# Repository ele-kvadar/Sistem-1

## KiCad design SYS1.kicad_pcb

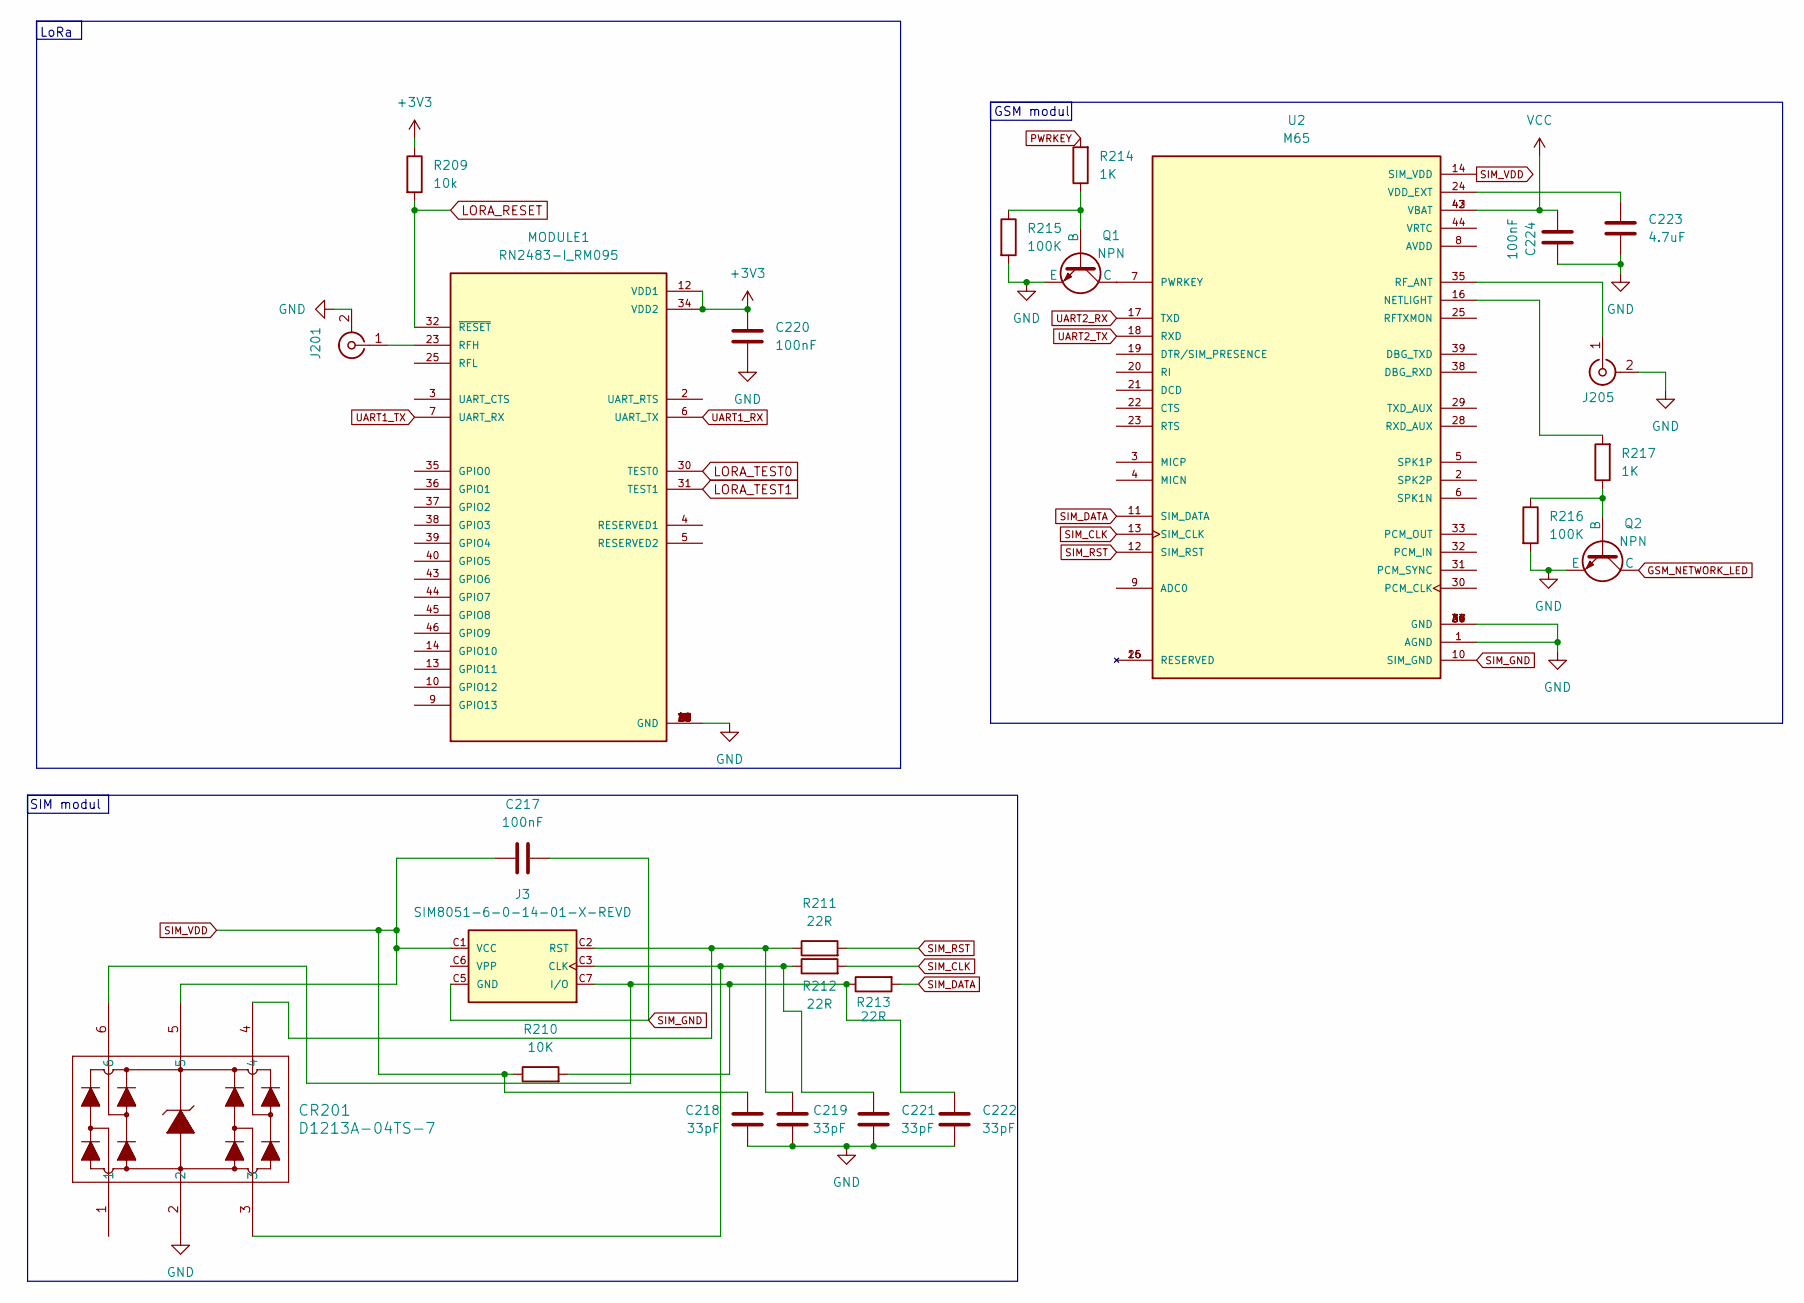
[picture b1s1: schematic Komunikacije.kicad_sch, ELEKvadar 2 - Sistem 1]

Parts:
C217, C220, C224: 100nF; C_1206_3216Metric_Pad1.33x1.80mm_HandSolder
C218, C219, C221, C222: 33pF; C_1206_3216Metric_Pad1.33x1.80mm_HandSolder
C223: 4.7uF; C_1206_3216Metric_Pad1.33x1.80mm_HandSolder
CR201: D1213A-04TS-7; TSOT26_DIO
J3: SIM8051-6-0-14-01-X-REVD; GCT_SIM8051-6-0-14-01-X-REVD
J201, J205: SMA_Amphenol_132134-16_Vertical
MODULE1: RN2483-I_RM095; MICROCHIP_RN2483-I_RM095
Q1, Q2: NPN; TSOT-23_HandSoldering
R209: 10k; R_1206_3216Metric_Pad1.30x1.75mm_HandSolder
R210: 10K; R_1206_3216Metric_Pad1.30x1.75mm_HandSolder
R211, R212, R213: 22R; R_1206_3216Metric_Pad1.30x1.75mm_HandSolder
R214, R217: 1K; R_1206_3216Metric_Pad1.30x1.75mm_HandSolder
R215, R216: 100K; R_1206_3216Metric_Pad1.30x1.75mm_HandSolder
U2: M65; XCVR_M65; PARTREV 1.0

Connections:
GND: C218.2, C219.2, C220.2, C221.2, C222.2, C223.1, C224.1, CR201.2, J201.2 (Ext), J205.2 (Ext), MODULE1.1 (GND), MODULE1.8 (GND), MODULE1.11 (GND), MODULE1.20 (GND), MODULE1.21 (GND), MODULE1.22 (GND), MODULE1.24 (GND), MODULE1.26 (GND), MODULE1.27 (GND), MODULE1.28 (GND), MODULE1.33 (GND), MODULE1.41 (GND), MODULE1.47 (GND), Q1.3 (E), Q2.3 (E), R215.2, R216.2, U2.1 (AGND), U2.27 (GND), U2.34 (GND), U2.36 (GND), U2.37 (GND), U2.40 (GND), U2.41 (GND); also elsewhere on the board
GSM_NETWORK_LED: Q2.1 (C); also elsewhere on the board
LORA_RESET: MODULE1.32 (~RESET), R209.2; also elsewhere on the board
LORA_TEST0: MODULE1.30 (TEST0); also elsewhere on the board
LORA_TEST1: MODULE1.31 (TEST1); also elsewhere on the board
unnamed: C221.1, CR201.3, J3.C3 (CLK), R212.1
unnamed: C222.1, CR201.6, J3.C7 (I/O), R210.2, R213.1
unnamed: C219.1, CR201.4, J3.C2 (RST), R211.1
unnamed: J201.1 (In), MODULE1.23 (RFH)
unnamed: J205.1 (In), U2.35 (RF_ANT)
unnamed: Q1.2 (B), R214.1, R215.1
unnamed: Q1.1 (C), U2.7 (PWRKEY)
unnamed: Q2.2 (B), R216.1, R217.1
unnamed: R217.2, U2.16 (NETLIGHT)
unnamed: C223.2, U2.24 (VDD_EXT)
PWRKEY: R214.2; also elsewhere on the board
SIM_CLK: R212.2, U2.13 (SIM_CLK)
SIM_DATA: R213.2, U2.11 (SIM_DATA)
SIM_GND: C217.2, J3.C5 (GND), U2.10 (SIM_GND)
SIM_RST: R211.2, U2.12 (SIM_RST)
SIM_VDD: C217.1, C218.1, CR201.5, J3.C1 (VCC), R210.1, U2.14 (SIM_VDD)
UART1_RX: MODULE1.6 (UART_TX); also elsewhere on the board
UART1_TX: MODULE1.7 (UART_RX); also elsewhere on the board
UART2_RX: U2.17 (TXD); also elsewhere on the board
UART2_TX: U2.18 (RXD); also elsewhere on the board
VCC: C224.2, U2.42 (VBAT), U2.43 (VBAT); also elsewhere on the board
VDDA: C220.1, MODULE1.12 (VDD1), MODULE1.34 (VDD2), R209.1; also elsewhere on the board

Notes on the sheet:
SIM modul
GSM modul
LoRa

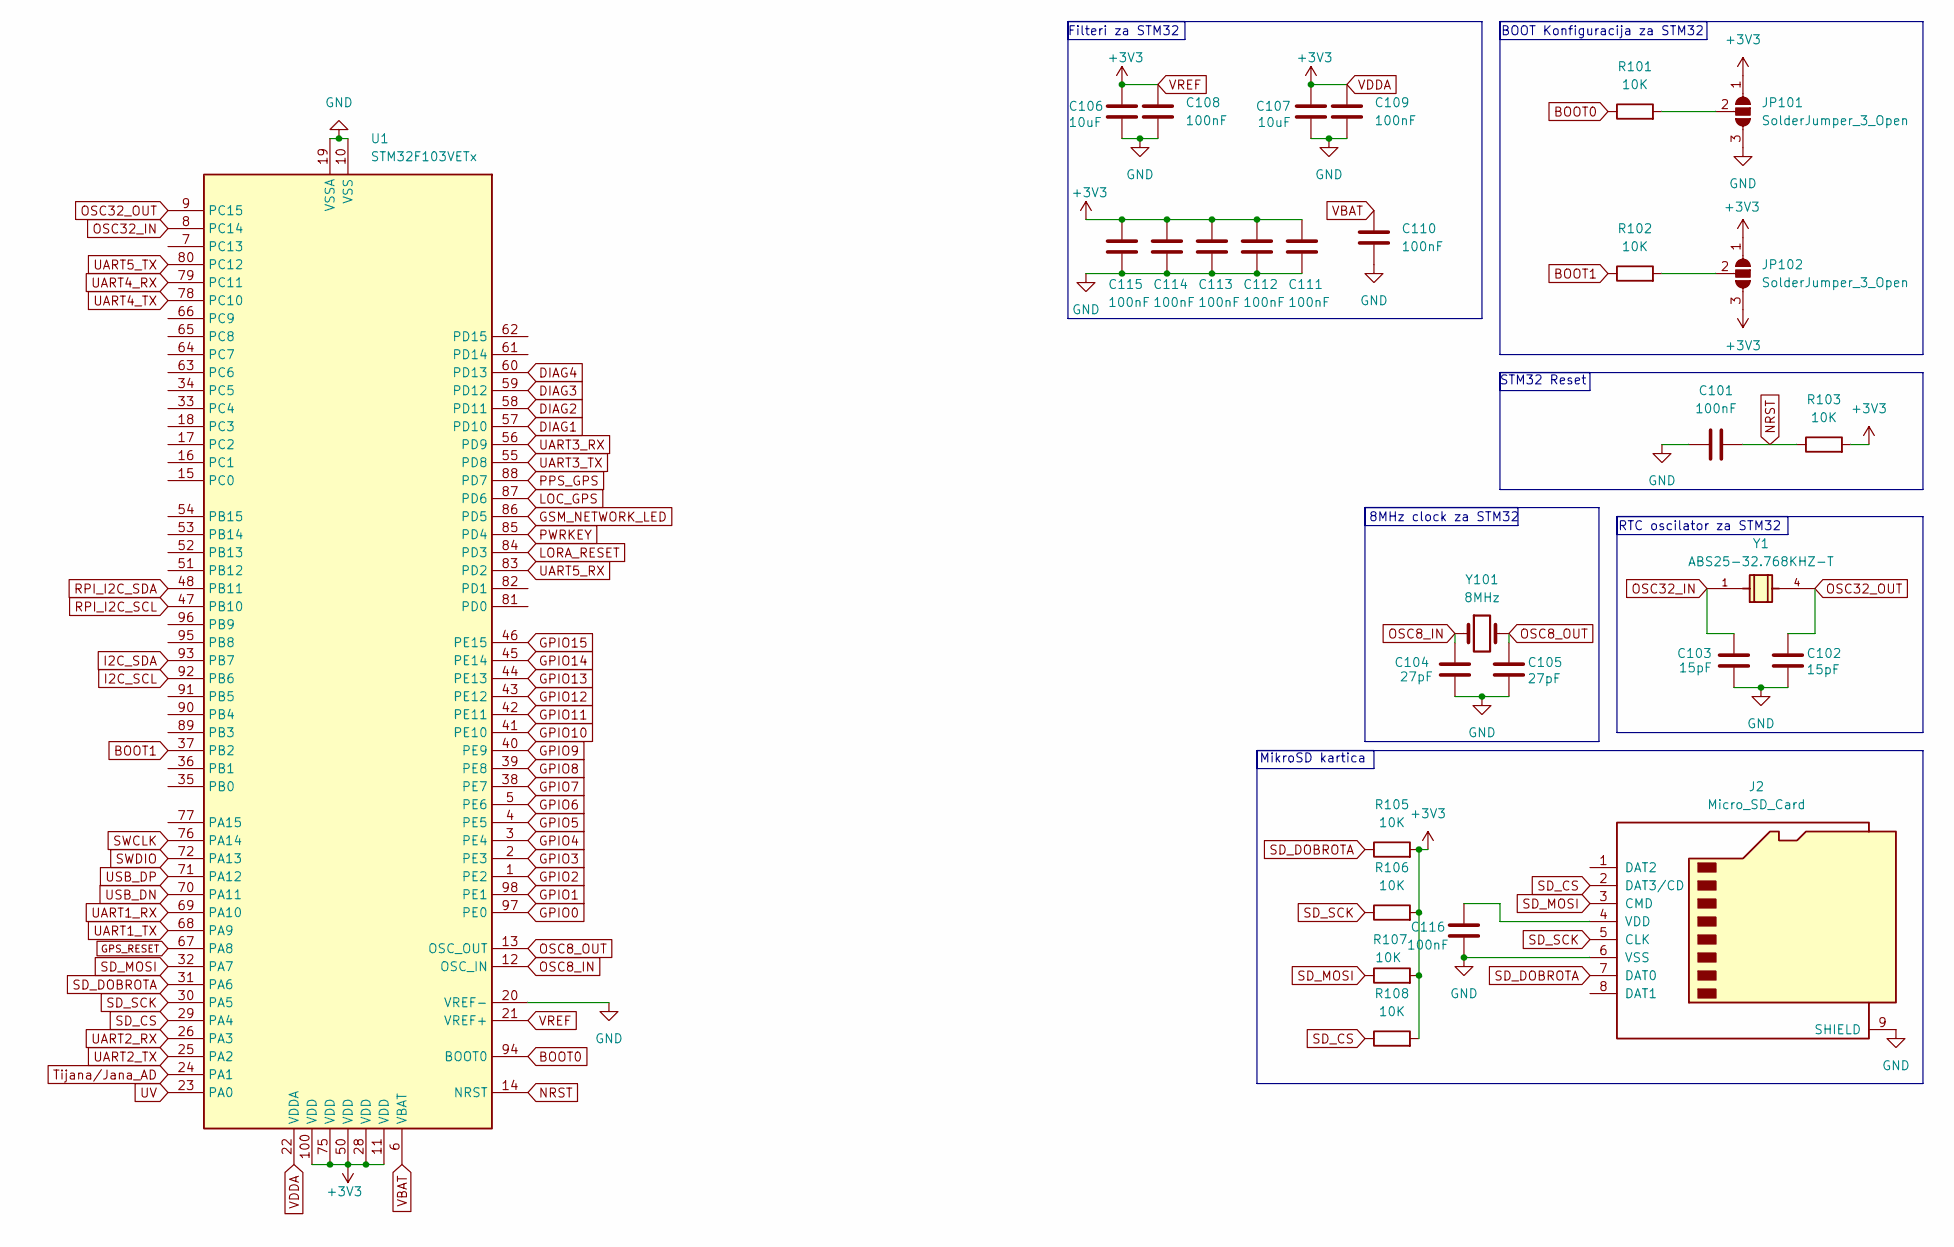
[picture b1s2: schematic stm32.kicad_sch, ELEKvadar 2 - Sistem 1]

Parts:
C101, C108, C109, C110, C111, C112, C113, C114, C115, C116: 100nF; C_1206_3216Metric_Pad1.33x1.80mm_HandSolder
C102, C103: 15pF; C_1206_3216Metric_Pad1.33x1.80mm_HandSolder
C104, C105: 27pF; C_1206_3216Metric_Pad1.33x1.80mm_HandSolder
C106, C107: 10uF; C_1206_3216Metric_Pad1.33x1.80mm_HandSolder
J2: Micro_SD_Card; microSD_HC_Molex_47219-2001
JP101, JP102: SolderJumper_3_Open; SolderJumper-3_P1.3mm_Open_RoundedPad1.0x1.5mm
R101, R102, R103, R105, R106, R107, R108: 10K; R_1206_3216Metric_Pad1.30x1.75mm_HandSolder
U1: STM32F103VETx; LQFP-100_14x14mm_P0.5mm
Y1: ABS25-32.768KHZ-T; Crystal_SMD_Abracon_ABS25-4Pin_8.0x3.8mm; PARTREV 12.01.15
Y101: 8MHz; Crystal_SMD_HC49-SD

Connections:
BOOT0: R101.1, U1.94 (BOOT0)
BOOT1: R102.1, U1.37 (PB2)
DIAG1: U1.57 (PD10); also elsewhere on the board
DIAG2: U1.58 (PD11); also elsewhere on the board
DIAG3: U1.59 (PD12); also elsewhere on the board
DIAG4: U1.60 (PD13); also elsewhere on the board
GND: C101.1, C102.2, C103.2, C104.2, C105.2, C106.2, C107.2, C108.1, C109.1, C110.1, C111.1, C112.1, C113.1, C114.1, C115.1, C116.1, J2.6 (VSS), J2.9 (SHIELD), JP101.3 (B), U1.10 (VSS), U1.19 (VSSA), U1.20 (VREF-), U1.27 (VSS), U1.49 (VSS), U1.74 (VSS), U1.99 (VSS); also elsewhere on the board
GPIO0: U1.97 (PE0); also elsewhere on the board
GPIO1: U1.98 (PE1); also elsewhere on the board
GPIO2: U1.1 (PE2); also elsewhere on the board
GPIO3: U1.2 (PE3); also elsewhere on the board
GPIO4: U1.3 (PE4); also elsewhere on the board
GPIO5: U1.4 (PE5); also elsewhere on the board
GPIO6: U1.5 (PE6); also elsewhere on the board
GPIO7: U1.38 (PE7); also elsewhere on the board
GPIO8: U1.39 (PE8); also elsewhere on the board
GPIO9: U1.40 (PE9); also elsewhere on the board
GPIO10: U1.41 (PE10); also elsewhere on the board
GPIO11: U1.42 (PE11); also elsewhere on the board
GPIO12: U1.43 (PE12); also elsewhere on the board
GPIO13: U1.44 (PE13); also elsewhere on the board
GPIO14: U1.45 (PE14); also elsewhere on the board
GPIO15: U1.46 (PE15); also elsewhere on the board
GPS_RESET: U1.67 (PA8); also elsewhere on the board
GSM_NETWORK_LED: U1.86 (PD5); also elsewhere on the board
I2C_SCL: U1.92 (PB6); also elsewhere on the board
I2C_SDA: U1.93 (PB7); also elsewhere on the board
LOC_GPS: U1.87 (PD6); also elsewhere on the board
LORA_RESET: U1.84 (PD3); also elsewhere on the board
NRST: C101.2, R103.1, U1.14 (NRST); also elsewhere on the board
unnamed: C116.2, J2.4 (VDD)
unnamed: JP101.2 (C), R101.2
unnamed: JP102.2 (C), R102.2
OSC8_IN: C104.1, U1.12 (OSC_IN), Y101.1
OSC8_OUT: C105.1, U1.13 (OSC_OUT), Y101.2
OSC32_IN: C103.1, U1.8 (PC14), Y1.1
OSC32_OUT: C102.1, U1.9 (PC15), Y1.4
PPS_GPS: U1.88 (PD7); also elsewhere on the board
PWRKEY: U1.85 (PD4); also elsewhere on the board
RPI_I2C_SCL: U1.47 (PB10); also elsewhere on the board
RPI_I2C_SDA: U1.48 (PB11); also elsewhere on the board
SD_CS: J2.2 (DAT3/CD), R108.1, U1.29 (PA4); also elsewhere on the board
SD_DOBROTA: J2.7 (DAT0), R105.1, U1.31 (PA6); also elsewhere on the board
SD_MOSI: J2.3 (CMD), R107.1, U1.32 (PA7); also elsewhere on the board
SD_SCK: J2.5 (CLK), R106.1, U1.30 (PA5); also elsewhere on the board
SWCLK: U1.76 (PA14); also elsewhere on the board
SWDIO: U1.72 (PA13); also elsewhere on the board
Tijana/Jana_AD: U1.24 (PA1); also elsewhere on the board
UART1_RX: U1.69 (PA10); also elsewhere on the board
UART1_TX: U1.68 (PA9); also elsewhere on the board
UART2_RX: U1.26 (PA3); also elsewhere on the board
UART2_TX: U1.25 (PA2); also elsewhere on the board
UART3_RX: U1.56 (PD9); also elsewhere on the board
UART3_TX: U1.55 (PD8); also elsewhere on the board
UART4_RX: U1.79 (PC11); also elsewhere on the board
UART4_TX: U1.78 (PC10); also elsewhere on the board
UART5_RX: U1.83 (PD2); also elsewhere on the board
UART5_TX: U1.80 (PC12); also elsewhere on the board
USB_DN: U1.70 (PA11); also elsewhere on the board
USB_DP: U1.71 (PA12); also elsewhere on the board
UV: U1.23 (PA0); also elsewhere on the board
VBAT: C110.2, U1.6 (VBAT); also elsewhere on the board
VDDA: C106.1, C107.1, C108.2, C109.2, C111.2, C112.2, C113.2, C114.2, C115.2, JP101.1 (A), JP102.1 (A), JP102.3 (B), R103.2, R105.2, R106.2, R107.2, R108.2, U1.11 (VDD), U1.21 (VREF+), U1.22 (VDDA), U1.28 (VDD), U1.50 (VDD), U1.75 (VDD), U1.100 (VDD); also elsewhere on the board

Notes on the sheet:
STM32 Reset
BOOT Konfiguracija za STM32
8MHz clock za STM32
Filteri za STM32
RTC oscilator za STM32
MikroSD kartica

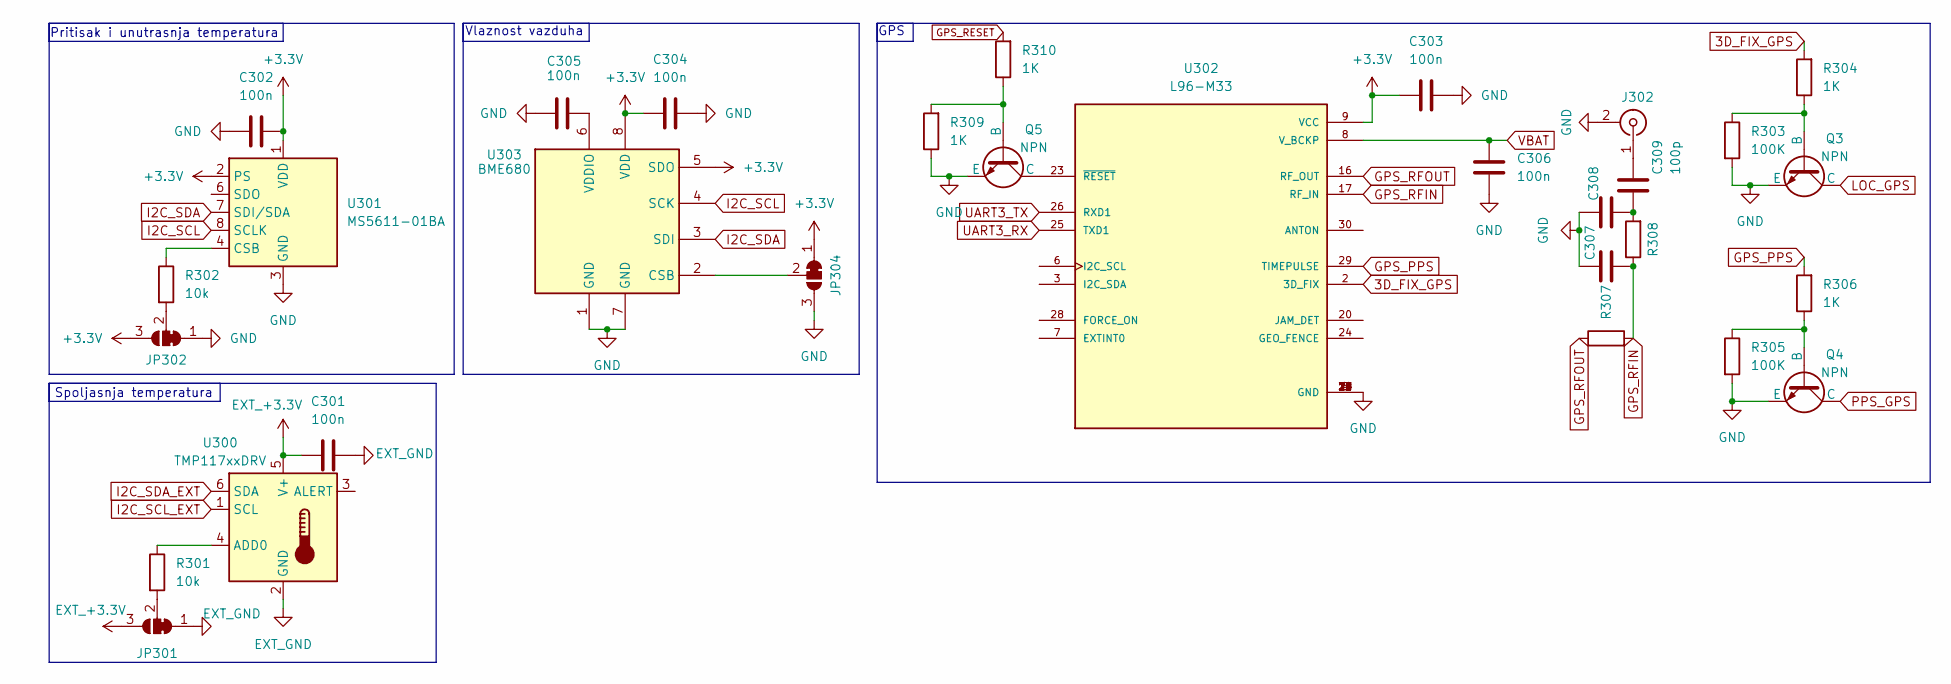
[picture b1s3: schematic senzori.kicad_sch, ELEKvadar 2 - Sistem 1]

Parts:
C301, C302, C303, C304, C305, C306: 100n; C_1206_3216Metric_Pad1.33x1.80mm_HandSolder
C307, C308: 0; C_1206_3216Metric_Pad1.33x1.80mm_HandSolder
C309: 100p; C_1206_3216Metric_Pad1.33x1.80mm_HandSolder
J302: SMA_Amphenol_132134-16_Vertical
JP301, JP302, JP304: SolderJumper_3_Bridged12; SolderJumper-3_P1.3mm_Bridged12_RoundedPad1.0x1.5mm
Q3, Q4, Q5: NPN; TSOT-23_HandSoldering
R301, R302: 10k; R_1206_3216Metric_Pad1.30x1.75mm_HandSolder
R303, R305: 100K; R_1206_3216Metric_Pad1.30x1.75mm_HandSolder
R304, R306, R309, R310: 1K; R_1206_3216Metric_Pad1.30x1.75mm_HandSolder
R307, R308: 0; R_1206_3216Metric_Pad1.30x1.75mm_HandSolder
U300: TMP117xxDRV; WSON-6-1EP_2x2mm_P0.65mm_EP1x1.6mm
U301: MS5611-01BA; LGA-8_3x5mm_P1.25mm
U302: L96-M33; Quectel_L96
U303: BME680; Bosch_LGA-8_3x3mm_P0.8mm_ClockwisePinNumbering

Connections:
3D_FIX_GPS: R304.2, U302.2 (3D_FIX)
+3.3V: C302.2, C303.1, C304.1, JP302.3 (B), JP304.1 (A), U301.1 (VDD), U301.2 (PS), U302.9 (VCC), U303.5 (SDO), U303.8 (VDD); also elsewhere on the board
EXT_+3.3V: C301.1, JP301.3 (B), U300.5 (V+); also elsewhere on the board
EXT_GND: C301.2, JP301.1 (A), U300.2 (GND); also elsewhere on the board
GND: C302.1, C303.2, C304.2, C305.2, C306.2, C307.1, C308.1, J302.2 (Ext), JP302.1 (A), JP304.3 (B), Q3.3 (E), Q4.3 (E), Q5.3 (E), R303.2, R305.2, R309.1, U301.3 (GND), U302.4 (GND), U302.5 (GND), U302.10 (GND), U302.11 (GND), U302.12 (GND), U302.13 (GND), U302.14 (GND), U302.15 (GND), U302.18 (GND), U302.19 (GND), U302.21 (GND), U302.22 (GND), U302.27 (GND), U302.31 (GND), U303.1 (GND), U303.7 (GND); also elsewhere on the board
GPS_PPS: R306.2, U302.29 (TIMEPULSE)
GPS_RESET: R310.2; also elsewhere on the board
GPS_RFIN: C307.2, R307.2, R308.1, U302.17 (RF_IN)
GPS_RFOUT: R307.1, U302.16 (RF_OUT)
I2C_SCL: U301.8 (SCLK), U303.4 (SCK); also elsewhere on the board
I2C_SCL_EXT: U300.1 (SCL); also elsewhere on the board
I2C_SDA: U301.7 (SDI/SDA), U303.3 (SDI); also elsewhere on the board
I2C_SDA_EXT: U300.6 (SDA); also elsewhere on the board
LOC_GPS: Q3.1 (C); also elsewhere on the board
unnamed: C308.2, C309.2, R308.2
unnamed: C309.1, J302.1 (In)
unnamed: JP301.2 (C), R301.2
unnamed: JP302.2 (C), R302.2
unnamed: JP304.2 (C), U303.2 (CSB)
unnamed: Q3.2 (B), R303.1, R304.1
unnamed: Q4.2 (B), R305.1, R306.1
unnamed: Q5.2 (B), R309.2, R310.1
unnamed: Q5.1 (C), U302.23 (~RESET)
unnamed: R302.1, U301.4 (CSB), U301.5 (CSB)
unnamed: R301.1, U300.4 (ADD0)
unnamed: C305.1, U303.6 (VDDIO)
PPS_GPS: Q4.1 (C); also elsewhere on the board
UART3_RX: U302.25 (TXD1); also elsewhere on the board
UART3_TX: U302.26 (RXD1); also elsewhere on the board
VBAT: C306.1, U302.8 (V_BCKP); also elsewhere on the board

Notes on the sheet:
GPS
Vlaznost vazduha
Pritisak i unutrasnja temperatura
Spoljasnja temperatura

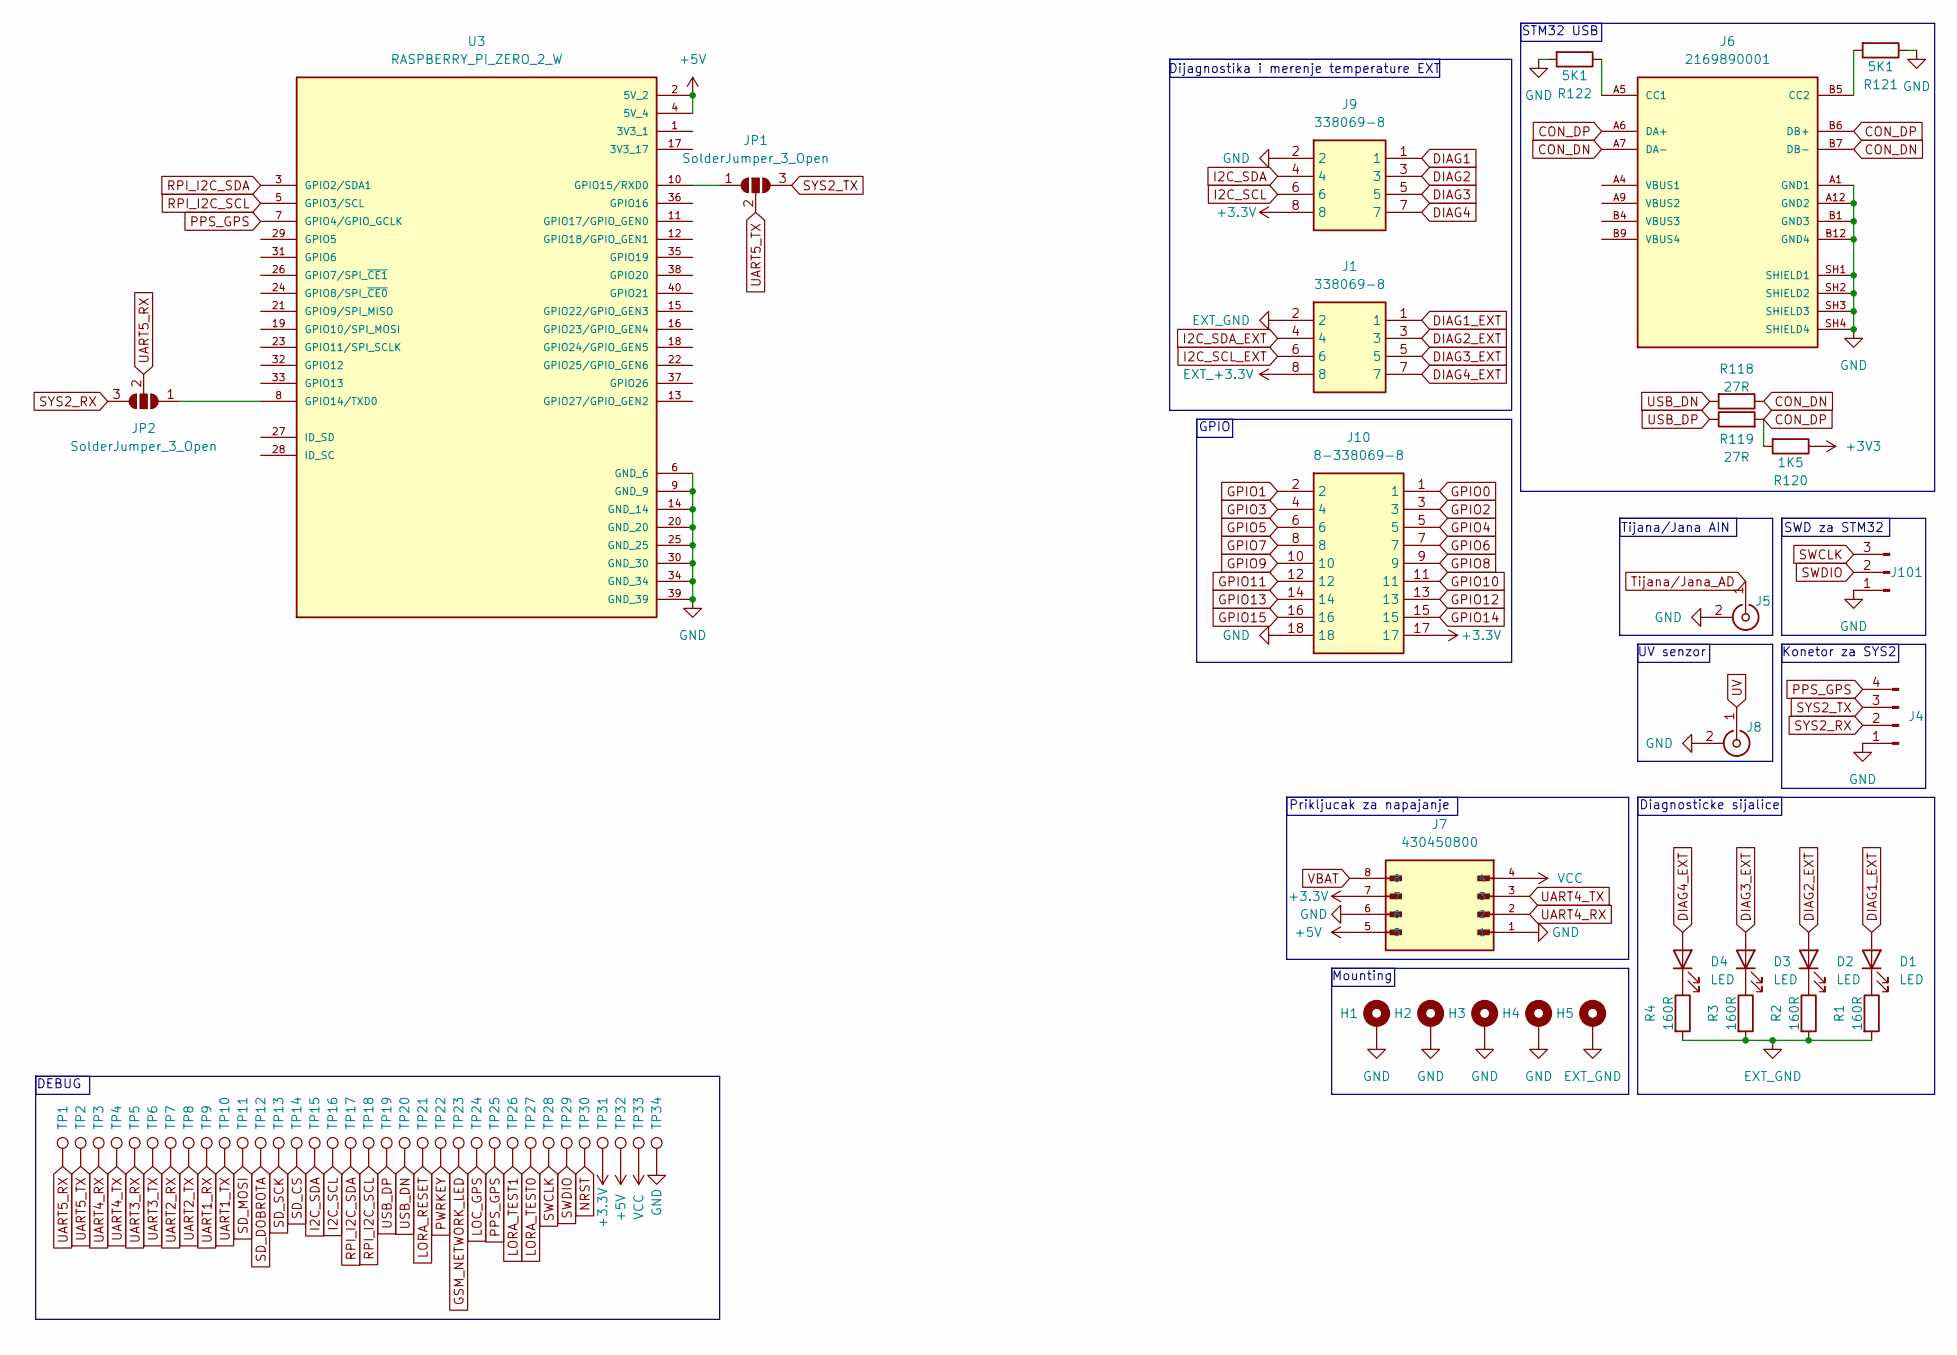
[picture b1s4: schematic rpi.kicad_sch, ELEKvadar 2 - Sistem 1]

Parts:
D1, D2, D3, D4: LED; LED_1206_3216Metric_Pad1.42x1.75mm_HandSolder
H1, H2, H3, H4, H5: MountingHole_Pad; MountingHole_3.2mm_M3_DIN965_Pad_TopBottom
J1, J9: 338069-8; 3380698; Mouser Part Number 571-338069-8
J4: Conn_01x04_Pin; Molex_Micro-Fit_3.0_43650-0400_1x04_P3.00mm_Horizontal
J5, J8: SMA_Amphenol_132134-16_Vertical
J6: 2169890001; MOLEX_2169890001; PARTREV B
J7: 430450800; MOLEX_430450800; PARTREV G
J10: 8-338069-8; 83380698; Manufacturer_Part_Number 8-338069-8; Mouser Part Number 571-8-338069-8
J101: Conn_01x03_Pin; PinHeader_1x03_P2.54mm_Vertical
JP1, JP2: SolderJumper_3_Open; SolderJumper-3_P1.3mm_Open_RoundedPad1.0x1.5mm
R1, R2, R3, R4: 160R; R_1206_3216Metric_Pad1.30x1.75mm_HandSolder
R118, R119: 27R; R_1206_3216Metric_Pad1.30x1.75mm_HandSolder
R120: 1K5; R_1206_3216Metric_Pad1.30x1.75mm_HandSolder
R121, R122: 5K1; R_1206_3216Metric_Pad1.30x1.75mm_HandSolder
TP1, TP2, TP3, TP4, TP5, TP6, TP7, TP8, TP9, TP10, TP11, TP12, TP13, TP14, TP15, TP16, TP17, TP18, TP19, TP20, TP21, TP22, TP23, TP24, TP25, TP26, TP27, TP28, TP29, TP30, TP31, TP32, TP33, TP34: TestPoint; TestPoint_Pad_D1.0mm
U3: RASPBERRY_PI_ZERO_2_W; MODULE_RASPBERRY_PI_ZERO_2_W; PARTREV April 2024

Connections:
+3.3V: J7.7, J9.8, J10.17, TP31.1; also elsewhere on the board
+5V: J7.5, TP32.1, U3.2 (5V_2), U3.4 (5V_4)
CON_DN: J6.A7 (DA-), J6.B7 (DB-), R118.1
CON_DP: J6.A6 (DA+), J6.B6 (DB+), R119.2, R120.2
DIAG1: J9.1; also elsewhere on the board
DIAG1_EXT: D1.2 (A), J1.1
DIAG2: J9.3; also elsewhere on the board
DIAG2_EXT: D2.2 (A), J1.3
DIAG3: J9.5; also elsewhere on the board
DIAG3_EXT: D3.2 (A), J1.5
DIAG4: J9.7; also elsewhere on the board
DIAG4_EXT: D4.2 (A), J1.7
EXT_+3.3V: J1.8; also elsewhere on the board
EXT_GND: H5.1, J1.2, R1.2, R2.2, R3.2, R4.2; also elsewhere on the board
GND: H1.1, H2.1, H3.1, H4.1, J4.1, J5.2 (Ext), J6.A1 (GND1), J6.A12 (GND2), J6.B1 (GND3), J6.B12 (GND4), J6.SH1 (SHIELD1), J6.SH2 (SHIELD2), J6.SH3 (SHIELD3), J6.SH4 (SHIELD4), J7.1, J7.6, J8.2 (Ext), J9.2, J10.18, J101.1, R121.1, R122.2, TP34.1, U3.6 (GND_6), U3.9 (GND_9), U3.14 (GND_14), U3.20 (GND_20), U3.25 (GND_25), U3.30 (GND_30), U3.34 (GND_34), U3.39 (GND_39); also elsewhere on the board
GPIO0: J10.1; also elsewhere on the board
GPIO1: J10.2; also elsewhere on the board
GPIO2: J10.3; also elsewhere on the board
GPIO3: J10.4; also elsewhere on the board
GPIO4: J10.5; also elsewhere on the board
GPIO5: J10.6; also elsewhere on the board
GPIO6: J10.7; also elsewhere on the board
GPIO7: J10.8; also elsewhere on the board
GPIO8: J10.9; also elsewhere on the board
GPIO9: J10.10; also elsewhere on the board
GPIO10: J10.11; also elsewhere on the board
GPIO11: J10.12; also elsewhere on the board
GPIO12: J10.13; also elsewhere on the board
GPIO13: J10.14; also elsewhere on the board
GPIO14: J10.15; also elsewhere on the board
GPIO15: J10.16; also elsewhere on the board
GSM_NETWORK_LED: TP23.1; also elsewhere on the board
I2C_SCL: J9.6, TP16.1; also elsewhere on the board
I2C_SCL_EXT: J1.6; also elsewhere on the board
I2C_SDA: J9.4, TP15.1; also elsewhere on the board
I2C_SDA_EXT: J1.4; also elsewhere on the board
LOC_GPS: TP24.1; also elsewhere on the board
LORA_RESET: TP21.1; also elsewhere on the board
LORA_TEST0: TP27.1; also elsewhere on the board
LORA_TEST1: TP26.1; also elsewhere on the board
NRST: TP30.1; also elsewhere on the board
unnamed: D1.1 (K), R1.1
unnamed: D2.1 (K), R2.1
unnamed: D3.1 (K), R3.1
unnamed: D4.1 (K), R4.1
unnamed: J6.A5 (CC1), R122.1
unnamed: J6.B5 (CC2), R121.2
unnamed: JP1.1 (A), U3.10 (GPIO15/RXD0)
unnamed: JP2.1 (A), U3.8 (GPIO14/TXD0)
PPS_GPS: J4.4, TP25.1, U3.7 (GPIO4/GPIO_GCLK); also elsewhere on the board
PWRKEY: TP22.1; also elsewhere on the board
RPI_I2C_SCL: TP18.1, U3.5 (GPIO3/SCL); also elsewhere on the board
RPI_I2C_SDA: TP17.1, U3.3 (GPIO2/SDA1); also elsewhere on the board
SD_CS: TP14.1; also elsewhere on the board
SD_DOBROTA: TP12.1; also elsewhere on the board
SD_MOSI: TP11.1; also elsewhere on the board
SD_SCK: TP13.1; also elsewhere on the board
SWCLK: J101.3, TP28.1; also elsewhere on the board
SWDIO: J101.2, TP29.1; also elsewhere on the board
SYS2_RX: J4.2, JP2.3 (B)
SYS2_TX: J4.3, JP1.3 (B)
Tijana/Jana_AD: J5.1 (In); also elsewhere on the board
UART1_RX: TP9.1; also elsewhere on the board
UART1_TX: TP10.1; also elsewhere on the board
UART2_RX: TP7.1; also elsewhere on the board
UART2_TX: TP8.1; also elsewhere on the board
UART3_RX: TP5.1; also elsewhere on the board
UART3_TX: TP6.1; also elsewhere on the board
UART4_RX: J7.2, TP3.1; also elsewhere on the board
UART4_TX: J7.3, TP4.1; also elsewhere on the board
UART5_RX: JP2.2 (C), TP1.1; also elsewhere on the board
UART5_TX: JP1.2 (C), TP2.1; also elsewhere on the board
USB_DN: R118.2, TP20.1; also elsewhere on the board
USB_DP: R119.1, TP19.1; also elsewhere on the board
UV: J8.1 (In); also elsewhere on the board
VBAT: J7.8; also elsewhere on the board
VCC: J7.4, TP33.1; also elsewhere on the board
VDDA: R120.1; also elsewhere on the board

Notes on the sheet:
SWD za STM32
Dijagnostika i merenje temperature EXT
DEBUG
Prikljucak za napajanje
Mounting
UV senzor
Konetor za SYS2
STM32 USB
Tijana/Jana AIN
GPIO
Diagnosticke sijalice

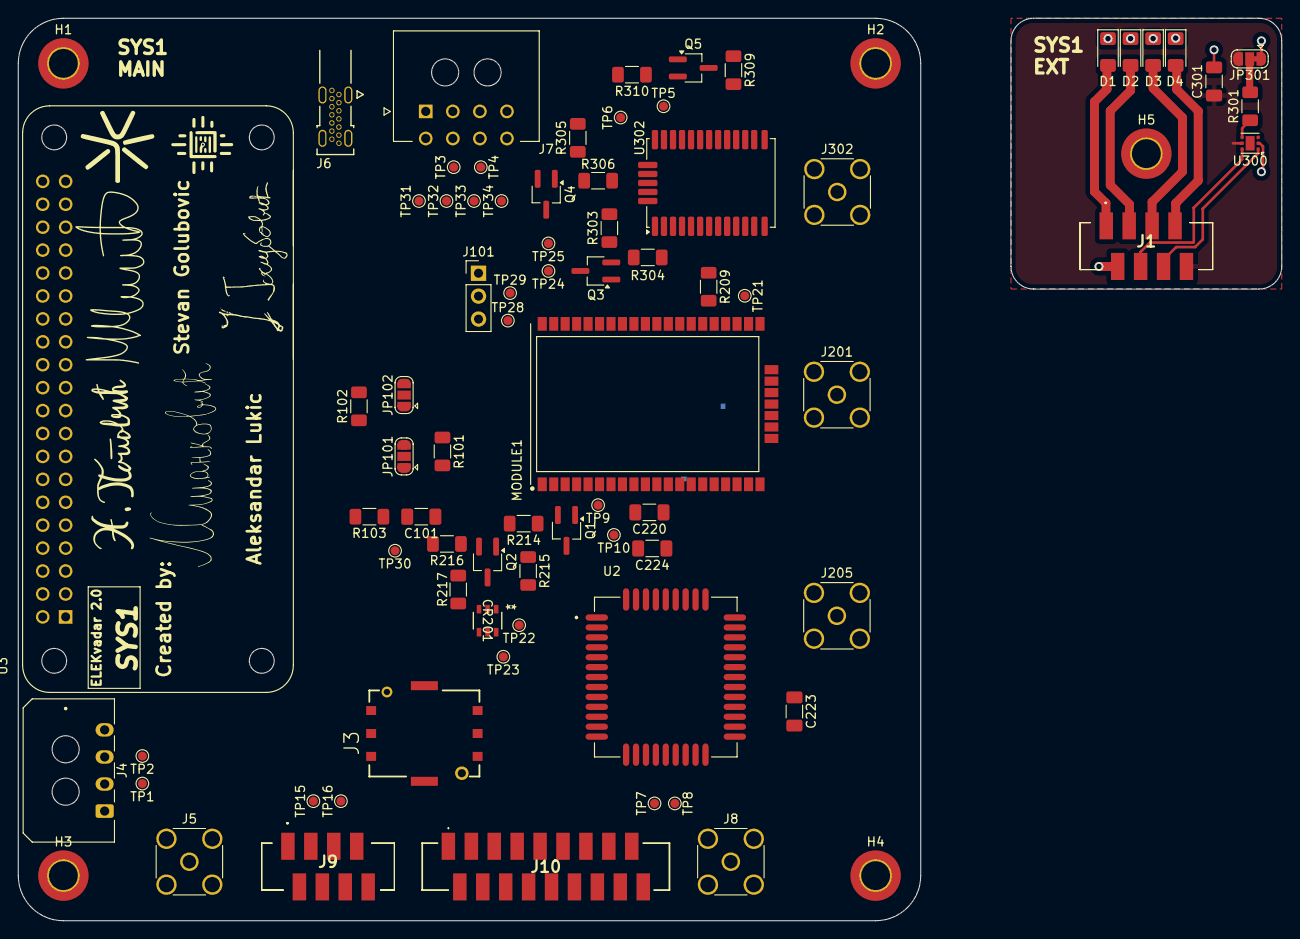
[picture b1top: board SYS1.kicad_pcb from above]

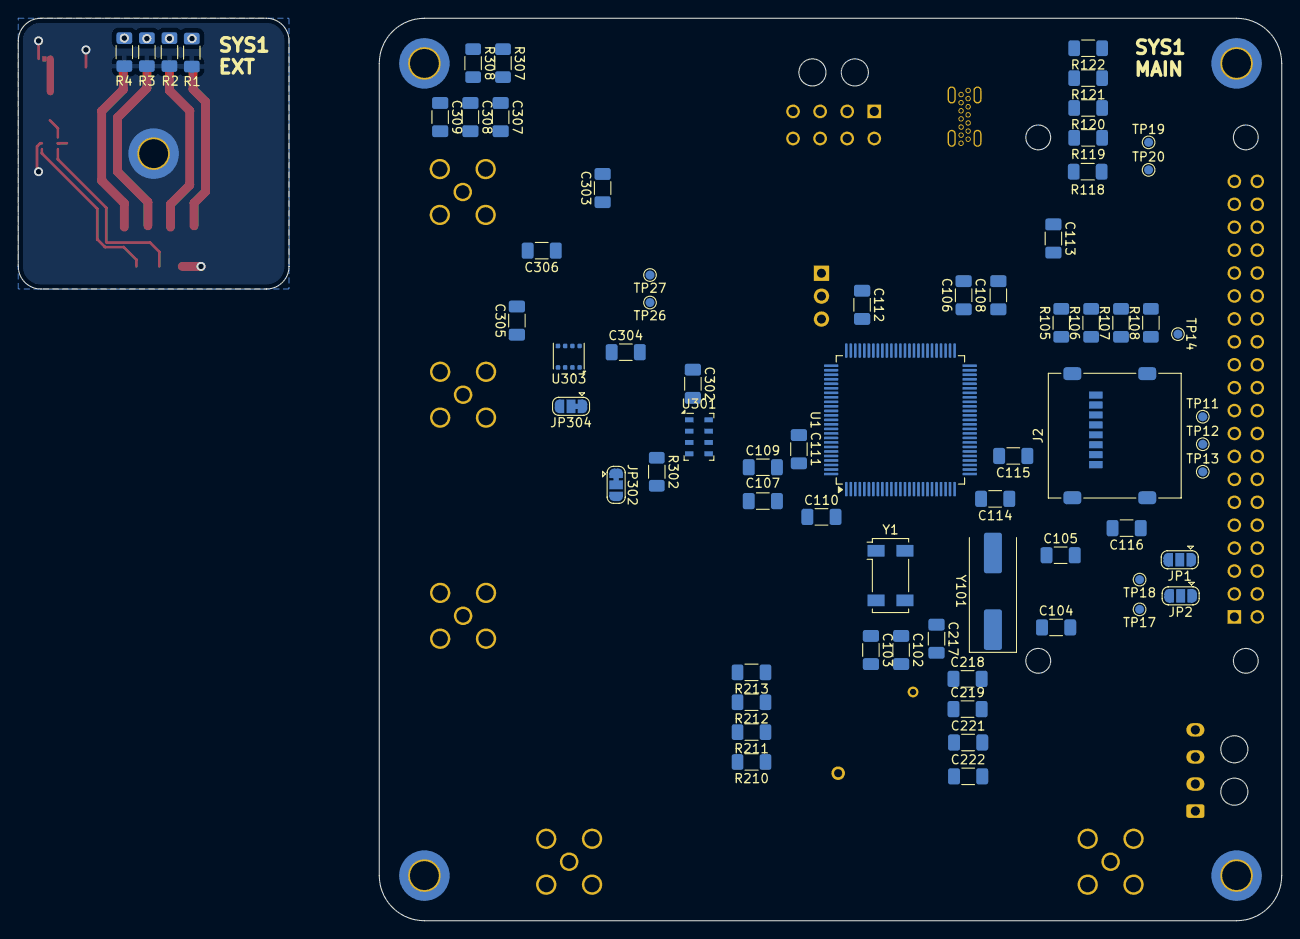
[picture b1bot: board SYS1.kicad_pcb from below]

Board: 4 copper layers, 140.0 x 100.0 mm, 148 parts (68 on the bottom side), 119 nets.

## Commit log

2025-05-30 Prva verzija seme
    Prva verzija sa svim semama objedinjenim bez pcb
2025-06-18 Pocetak PCB dizajna
    Dodao fizicke definicije ploce
    Dodao rupe za montazu
    Kreirao inicijalnijalni placement
2025-06-18 Napajanje
    David i njegova biblioteka su pravili probleme
2025-06-18 manje izmene pcb layouta
    dodao konektor za napajanje
2025-06-19 Znacajne izmene seme
    Dodao prikljucak za UV senzor
    Dodao reset za GPS
    Dodao ext_ant za GPS
    Dodao 3D modele
    Dodao testpoint-e
    Sredio semu malo
2025-06-19 H2 se pomerio i izmenio RPI footprint
    Pomerio mountng hole H2 da se poracna sa mounting hole na rpi
    Nova pozicija je 5mm od leve ivice 7mm od gornje
    Izmenio sam footprint za rpi da uklonim 2 rupe koje se nalaze na desnoj ivici zato sto nam nisu potrebne
2025-06-19 Manje izmene PCB
    Podesio plocu da bude 4 sloja
2025-06-19 Layout i rutiranje za EXT PCB uradjeni
    Uradio sam layout i rutiranje za plocicu sa sijalicama i senzorom temperature koja ce biti montirana napolju
2025-06-19 Dodata baterija
    Dodao pin za bateriju na konektor za napajanje
2025-06-19 Manje izmene seme
    Sredio izgled seme
2025-07-03 Znacajne izmene seme i pcb-a
    Napravljen nov layout
    dodat konektor za gpio
    dodat konektor za eksterna merenja vetra
    izmenjene diag lampice
    izmenjen konektor za ext plocu
    razno
2025-07-04 Velike izmene PCB
    Zavrsena mala spoljanja plocica
    Preliminarni placement komponenti na velikoj plocici
    Dodati logotipi ISP i ELE
    Dodato potpise
